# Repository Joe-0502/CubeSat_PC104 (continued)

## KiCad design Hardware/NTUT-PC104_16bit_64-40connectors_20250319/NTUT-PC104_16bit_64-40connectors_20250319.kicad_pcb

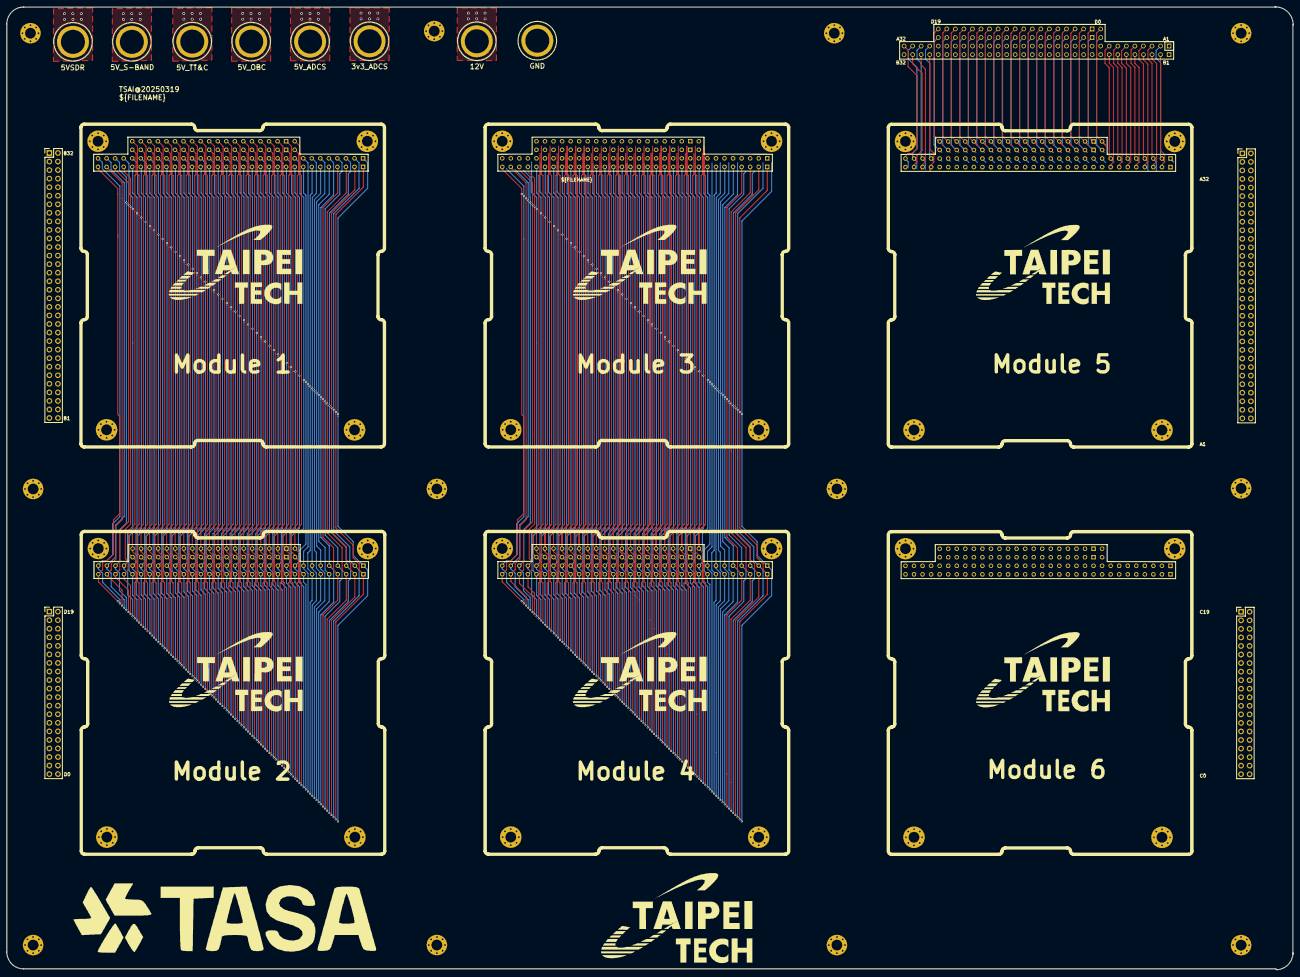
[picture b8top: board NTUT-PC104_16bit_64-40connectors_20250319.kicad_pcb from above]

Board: 4 copper layers, 382.2 x 286.1 mm, 31 parts (0 on the bottom side), 104 nets.

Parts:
H7, H7#2, H8, H9, H10, H11, H12, H13, H14, H15, H15#2, H15#3: MountingHole_Pad; MountingHole_3.2mm_M3_Pad_Via
J9, J9#2, J10, J11, J11#2, J12: CubeSat_PC104_16bit_footprint
J13: PC104_16bit_Connector
J17, J19: Conn_02x26_Odd_Even; PinHeader_2x32_P2.54mm_Vertical
J18, J20: Conn_02x26_Odd_Even; PinHeader_2x20_P2.54mm_Vertical
TP9, TP9#2, TP9#3, TP10, TP10#2, TP10#3, TP11, TP12: TestPoint_Alt; KSE_PN6095

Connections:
/A1: J9.A1, J9#2.A1, J10.A1, J11.A1, J11#2.A1, J12.A1, J13.A1, J17.63, J19.63
/A2: J9.A2, J9#2.A2, J10.A2, J11.A2, J11#2.A2, J12.A2, J13.A2, J17.61, J19.61
/A3: J9.A3, J9#2.A3, J10.A3, J11.A3, J11#2.A3, J12.A3, J13.A3, J17.59, J19.59
/A4: J9.A4, J9#2.A4, J10.A4, J11.A4, J11#2.A4, J12.A4, J13.A4, J17.57, J19.57
/A5: J9.A5, J9#2.A5, J10.A5, J11.A5, J11#2.A5, J12.A5, J13.A5, J17.55, J19.55
/A6: J9.A6, J9#2.A6, J10.A6, J11.A6, J11#2.A6, J12.A6, J13.A6, J17.53, J19.53
/A7: J9.A7, J9#2.A7, J10.A7, J11.A7, J11#2.A7, J12.A7, J13.A7, J17.51, J19.51
/A8: J9.A8, J9#2.A8, J10.A8, J11.A8, J11#2.A8, J12.A8, J13.A8, J17.49, J19.49
/A9: J9.A9, J9#2.A9, J10.A9, J11.A9, J11#2.A9, J12.A9, J13.A9, J17.47, J19.47
/A10: J9.A10, J9#2.A10, J10.A10, J11.A10, J11#2.A10, J12.A10, J13.A10, J17.45, J19.45
/A11: J9.A11, J9#2.A11, J10.A11, J11.A11, J11#2.A11, J12.A11, J13.A11, J17.43, J19.43
/A12: J9.A12, J9#2.A12, J10.A12, J11.A12, J11#2.A12, J12.A12, J13.A12, J17.41, J19.41
/A13: J9.A13, J9#2.A13, J10.A13, J11.A13, J11#2.A13, J12.A13, J13.A13, J17.39, J19.39
/A14: J9.A14, J9#2.A14, J10.A14, J11.A14, J11#2.A14, J12.A14, J13.A14, J17.37, J19.37
/A15: J9.A15, J9#2.A15, J10.A15, J11.A15, J11#2.A15, J12.A15, J13.A15, J17.35, J19.35
/A16: J9.A16, J9#2.A16, J10.A16, J11.A16, J11#2.A16, J12.A16, J13.A16, J17.33, J19.33
/A17: J9.A17, J9#2.A17, J10.A17, J11.A17, J11#2.A17, J12.A17, J13.A17, J17.31, J19.31
/A18: J9.A18, J9#2.A18, J10.A18, J11.A18, J11#2.A18, J12.A18, J13.A18, J17.29, J19.29
/A19: J9.A19, J9#2.A19, J10.A19, J11.A19, J11#2.A19, J12.A19, J13.A19, J17.27, J19.27
/A20: J9.A20, J9#2.A20, J10.A20, J11.A20, J11#2.A20, J12.A20, J13.A20, J17.25, J19.25
/A21: J9.A21, J9#2.A21, J10.A21, J11.A21, J11#2.A21, J12.A21, J13.A21, J17.23, J19.23
/A22: J9.A22, J9#2.A22, J10.A22, J11.A22, J11#2.A22, J12.A22, J13.A22, J17.21, J19.21
/A23: J9.A23, J9#2.A23, J10.A23, J11.A23, J11#2.A23, J12.A23, J13.A23, J17.19, J19.19
/A24: J9.A24, J9#2.A24, J10.A24, J11.A24, J11#2.A24, J12.A24, J13.A24, J17.17, J19.17
/A25: J9.A25, J9#2.A25, J10.A25, J11.A25, J11#2.A25, J12.A25, J13.A25, J17.15, J19.15
/A26: J9.A26, J9#2.A26, J10.A26, J11.A26, J11#2.A26, J12.A26, J13.A26, J17.13, J19.13
/A27: J9.A27, J9#2.A27, J10.A27, J11.A27, J11#2.A27, J12.A27, J13.A27, J17.11, J19.11
/A28: J9.A28, J9#2.A28, J10.A28, J11.A28, J11#2.A28, J12.A28, J13.A28, J17.9, J19.9
/A29: J9.A29, J9#2.A29, J10.A29, J11.A29, J11#2.A29, J12.A29, J13.A29, J17.7, J19.7
/A30: J9.A30, J9#2.A30, J10.A30, J11.A30, J11#2.A30, J12.A30, J13.A30, J17.5, J19.5
/A31: J9.A31, J9#2.A31, J10.A31, J11.A31, J11#2.A31, J12.A31, J13.A31, J17.3, J19.3
/A32: J9.A32, J9#2.A32, J10.A32, J11.A32, J11#2.A32, J12.A32, J13.A32, J17.1, J19.1
/B1: J9.B1, J9#2.B1, J10.B1, J11.B1, J11#2.B1, J12.B1, J13.B1, J17.64, J19.64
/B2: J9.B2, J9#2.B2, J10.B2, J11.B2, J11#2.B2, J12.B2, J13.B2, J17.62, J19.62
/B3: J9.B3, J9#2.B3, J10.B3, J11.B3, J11#2.B3, J12.B3, J13.B3, J17.60, J19.60
/B4: J9.B4, J9#2.B4, J10.B4, J11.B4, J11#2.B4, J12.B4, J13.B4, J17.58, J19.58
/B5: J9.B5, J9#2.B5, J10.B5, J11.B5, J11#2.B5, J12.B5, J13.B5, J17.56, J19.56
/B6: J9.B6, J9#2.B6, J10.B6, J11.B6, J11#2.B6, J12.B6, J13.B6, J17.54, J19.54
/B7: J9.B7, J9#2.B7, J10.B7, J11.B7, J11#2.B7, J12.B7, J13.B7, J17.52, J19.52
/B8: J9.B8, J9#2.B8, J10.B8, J11.B8, J11#2.B8, J12.B8, J13.B8, J17.50, J19.50
/B9: J9.B9, J9#2.B9, J10.B9, J11.B9, J11#2.B9, J12.B9, J13.B9, J17.48, J19.48
/B10: J9.B10, J9#2.B10, J10.B10, J11.B10, J11#2.B10, J12.B10, J13.B10, J17.46, J19.46
/B11: J9.B11, J9#2.B11, J10.B11, J11.B11, J11#2.B11, J12.B11, J13.B11, J17.44, J19.44
/B12: J9.B12, J9#2.B12, J10.B12, J11.B12, J11#2.B12, J12.B12, J13.B12, J17.42, J19.42
/B13: J9.B13, J9#2.B13, J10.B13, J11.B13, J11#2.B13, J12.B13, J13.B13, J17.40, J19.40
/B14: J9.B14, J9#2.B14, J10.B14, J11.B14, J11#2.B14, J12.B14, J13.B14, J17.38, J19.38
/B15: J9.B15, J9#2.B15, J10.B15, J11.B15, J11#2.B15, J12.B15, J13.B15, J17.36, J19.36
/B16: J9.B16, J9#2.B16, J10.B16, J11.B16, J11#2.B16, J12.B16, J13.B16, J17.34, J19.34
/B17: J9.B17, J9#2.B17, J10.B17, J11.B17, J11#2.B17, J12.B17, J13.B17, J17.32, J19.32
/B18: J9.B18, J9#2.B18, J10.B18, J11.B18, J11#2.B18, J12.B18, J13.B18, J17.30, J19.30
/B19: J9.B19, J9#2.B19, J10.B19, J11.B19, J11#2.B19, J12.B19, J13.B19, J17.28, J19.28
/B20: J9.B20, J9#2.B20, J10.B20, J11.B20, J11#2.B20, J12.B20, J13.B20, J17.26, J19.26
/B21: J9.B21, J9#2.B21, J10.B21, J11.B21, J11#2.B21, J12.B21, J13.B21, J17.24, J19.24
/B22: J9.B22, J9#2.B22, J10.B22, J11.B22, J11#2.B22, J12.B22, J13.B22, J17.22, J19.22
/B23: J9.B23, J9#2.B23, J10.B23, J11.B23, J11#2.B23, J12.B23, J13.B23, J17.20, J19.20
/B24: J9.B24, J9#2.B24, J10.B24, J11.B24, J11#2.B24, J12.B24, J13.B24, J17.18, J19.18
/B25: J9.B25, J9#2.B25, J10.B25, J11.B25, J11#2.B25, J12.B25, J13.B25, J17.16, J19.16
/B26: J9.B26, J9#2.B26, J10.B26, J11.B26, J11#2.B26, J12.B26, J13.B26, J17.14, J19.14
/B27: J9.B27, J9#2.B27, J10.B27, J11.B27, J11#2.B27, J12.B27, J13.B27, J17.12, J19.12
/B28: J9.B28, J9#2.B28, J10.B28, J11.B28, J11#2.B28, J12.B28, J13.B28, J17.10, J19.10
/B29: J9.B29, J9#2.B29, J10.B29, J11.B29, J11#2.B29, J12.B29, J13.B29, J17.8, J19.8
/B30: J9.B30, J9#2.B30, J10.B30, J11.B30, J11#2.B30, J12.B30, J13.B30, J17.6, J19.6
/B31: J9.B31, J9#2.B31, J10.B31, J11.B31, J11#2.B31, J12.B31, J13.B31, J17.4, J19.4
/B32: J9.B32, J9#2.B32, J10.B32, J11.B32, J11#2.B32, J12.B32, J13.B32, J17.2, J19.2
/C0: J9.C0, J9#2.C0, J10.C0, J11.C0, J11#2.C0, J12.C0, J13.C0, J18.39, J20.39
/C1: J9.C1, J9#2.C1, J10.C1, J11.C1, J11#2.C1, J12.C1, J13.C1, J18.37, J20.37
/C2: J9.C2, J9#2.C2, J10.C2, J11.C2, J11#2.C2, J12.C2, J13.C2, J18.35, J20.35
/C3: J9.C3, J9#2.C3, J10.C3, J11.C3, J11#2.C3, J12.C3, J13.C3, J18.33, J20.33
/C4: J9.C4, J9#2.C4, J10.C4, J11.C4, J11#2.C4, J12.C4, J13.C4, J18.31, J20.31
/C5: J9.C5, J9#2.C5, J10.C5, J11.C5, J11#2.C5, J12.C5, J13.C5, J18.29, J20.29
/C6: J9.C6, J9#2.C6, J10.C6, J11.C6, J11#2.C6, J12.C6, J13.C6, J18.27, J20.27
/C7: J9.C7, J9#2.C7, J10.C7, J11.C7, J11#2.C7, J12.C7, J13.C7, J18.25, J20.25
/C8: J9.C8, J9#2.C8, J10.C8, J11.C8, J11#2.C8, J12.C8, J13.C8, J18.23, J20.23
/C9: J9.C9, J9#2.C9, J10.C9, J11.C9, J11#2.C9, J12.C9, J13.C9, J18.21, J20.21
/C10: J9.C10, J9#2.C10, J10.C10, J11.C10, J11#2.C10, J12.C10, J13.C10, J18.19, J20.19
/C11: J9.C11, J9#2.C11, J10.C11, J11.C11, J11#2.C11, J12.C11, J13.C11, J18.17, J20.17
/C12: J9.C12, J9#2.C12, J10.C12, J11.C12, J11#2.C12, J12.C12, J13.C12, J18.15, J20.15
/C13: J9.C13, J9#2.C13, J10.C13, J11.C13, J11#2.C13, J12.C13, J13.C13, J18.13, J20.13
/C14: J9.C14, J9#2.C14, J10.C14, J11.C14, J11#2.C14, J12.C14, J13.C14, J18.11, J20.11
/C15: J9.C15, J9#2.C15, J10.C15, J11.C15, J11#2.C15, J12.C15, J13.C15, J18.9, J20.9
/C16: J9.C16, J9#2.C16, J10.C16, J11.C16, J11#2.C16, J12.C16, J13.C16, J18.7, J20.7
/C17: J9.C17, J9#2.C17, J10.C17, J11.C17, J11#2.C17, J12.C17, J13.C17, J18.5, J20.5
/C18: J9.C18, J9#2.C18, J10.C18, J11.C18, J11#2.C18, J12.C18, J13.C18, J18.3, J20.3
/C19: J9.C19, J9#2.C19, J10.C19, J11.C19, J11#2.C19, J12.C19, J13.C19, J18.1, J20.1
/D0: J9.D0, J9#2.D0, J10.D0, J11.D0, J11#2.D0, J12.D0, J13.D0, J18.40, J20.40
/D1: J9.D1, J9#2.D1, J10.D1, J11.D1, J11#2.D1, J12.D1, J13.D1, J18.38, J20.38
/D2: J9.D2, J9#2.D2, J10.D2, J11.D2, J11#2.D2, J12.D2, J13.D2, J18.36, J20.36
/D3: J9.D3, J9#2.D3, J10.D3, J11.D3, J11#2.D3, J12.D3, J13.D3, J18.34, J20.34
/D4: J9.D4, J9#2.D4, J10.D4, J11.D4, J11#2.D4, J12.D4, J13.D4, J18.32, J20.32
/D5: J9.D5, J9#2.D5, J10.D5, J11.D5, J11#2.D5, J12.D5, J13.D5, J18.30, J20.30
/D6: J9.D6, J9#2.D6, J10.D6, J11.D6, J11#2.D6, J12.D6, J13.D6, J18.28, J20.28
/D7: J9.D7, J9#2.D7, J10.D7, J11.D7, J11#2.D7, J12.D7, J13.D7, J18.26, J20.26
/D8: J9.D8, J9#2.D8, J10.D8, J11.D8, J11#2.D8, J12.D8, J13.D8, J18.24, J20.24
/D9: J9.D9, J9#2.D9, J10.D9, J11.D9, J11#2.D9, J12.D9, J13.D9, J18.22, J20.22
/D10: J9.D10, J9#2.D10, J10.D10, J11.D10, J11#2.D10, J12.D10, J13.D10, J18.20, J20.20
/D11: J9.D11, J9#2.D11, J10.D11, J11.D11, J11#2.D11, J12.D11, J13.D11, J18.18, J20.18
/D12: J9.D12, J9#2.D12, J10.D12, J11.D12, J11#2.D12, J12.D12, J13.D12, J18.16, J20.16
/D13: J9.D13, J9#2.D13, J10.D13, J11.D13, J11#2.D13, J12.D13, J13.D13, J18.14, J20.14
/D14: J9.D14, J9#2.D14, J10.D14, J11.D14, J11#2.D14, J12.D14, J13.D14, J18.12, J20.12
/D15: J9.D15, J9#2.D15, J10.D15, J11.D15, J11#2.D15, J12.D15, J13.D15, J18.10, J20.10
/D16: J9.D16, J9#2.D16, J10.D16, J11.D16, J11#2.D16, J12.D16, J13.D16, J18.8, J20.8
/D17: J9.D17, J9#2.D17, J10.D17, J11.D17, J11#2.D17, J12.D17, J13.D17, J18.6, J20.6
/D18: J9.D18, J9#2.D18, J10.D18, J11.D18, J11#2.D18, J12.D18, J13.D18, J18.4, J20.4
/D19: J9.D19, J9#2.D19, J10.D19, J11.D19, J11#2.D19, J12.D19, J13.D19, J18.2, J20.2

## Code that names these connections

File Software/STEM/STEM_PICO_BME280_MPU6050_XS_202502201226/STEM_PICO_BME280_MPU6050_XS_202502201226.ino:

// code for Pro Micro or STM32 on the CubeSat Simulator STEM Payload board
// answers "OK" on the serial port Serial1 when queried by the Pi

#include <Wire.h>
#include <Adafruit_Sensor.h>
#include <Adafruit_BME280.h>
#include <MPU6050_tockn.h>
#include <EEPROM.h>
#define SEALEVELPRESSURE_HPA (1013.25)


// Code modified for STEM board with PICO 

// PI_TXD       : GPIO0   using Serial1()
// PI_RXD       : GPIO1
// TX2          : GPIO8   using Serial2()
// RX2          : GPIO9
// LED1(G)      : GPIO17
// LED2(B)      : GPIO16
// LED(BUILT_IN): GPIO14

// I2C0_SDA     : GPIO12
// I2C0_SCL     : GPIO13
// I2C1_SDA     : GPIO6
// I2C1_SCL     : GPIO7

Adafruit_BME280 bme;
MPU6050 mpu6050(Wire);


long timer = 0;
int bmePresent;
int RXLED = LED_BUILTIN;  // The RX LED has a defined Arduino pin
int greenLED = 19;
int blueLED = 18;
int Sensor1 = 0;
float Sensor2 = 0;
void eeprom_word_write(int addr, int val);
short eeprom_word_read(int addr);
int first_time = true;
int first_read = true;

float T2 = 25; // Temperature data point 1
float R2 = 671; // Reading data point 1
float T1 = 15.5; // Temperature data point 2
float R1 = 695; // Reading data point 2


int sensorValue;
float Temp;
float rest;
  
void setup() {

  Serial2.begin(115200); // Serial Monitor for testing
  Serial1.begin(115200);  // UART1 faster speed
  Serial2.println("UART1: Starting!");

  Wire.setSCL(13);
  Wire.setSDA(12);
  Wire.begin();
  
  blink_setup();
 
  blink(500);
  delay(250);
  blink(500);
  delay(250);
  led_set(greenLED, HIGH);
  delay(250);
  led_set(greenLED, LOW);
  led_set(blueLED, HIGH);
  delay(250);
  led_set(blueLED, LOW);

  if (bme.begin(0x76)) {
    bmePresent = 1;
  } else {
    Serial2.println("UART1: Could not find a valid BME280 sensor, check wiring!");
    bmePresent = 0;
  }
 
  mpu6050.begin();
 
  if (eeprom_word_read(0) == 0xA07)
  {
    Serial2.println("UART1: Reading gyro offsets from EEPROM\n");
 
    float xOffset = ((float)eeprom_word_read(1)) / 100.0;
    float yOffset = ((float)eeprom_word_read(2)) / 100.0;
    float zOffset = ((float)eeprom_word_read(3)) / 100.0;
 
    Serial2.println(xOffset, DEC);
    Serial2.println(yOffset, DEC);
    Serial2.println(zOffset, DEC);
 
    mpu6050.setGyroOffsets(xOffset, yOffset, zOffset);
  }
  else
  {
    Serial2.println("UART1: Calculating gyro offsets and storing in EEPROM\n");
 
    mpu6050.calcGyroOffsets(true);
 
    eeprom_word_write(0, 0xA07);
    eeprom_word_write(1, (int)(mpu6050.getGyroXoffset() * 100.0) + 0.5);
    eeprom_word_write(2, (int)(mpu6050.getGyroYoffset() * 100.0) + 0.5);
    eeprom_word_write(3, (int)(mpu6050.getGyroZoffset() * 100.0) + 0.5);
 
    Serial2.println(eeprom_word_read(0), HEX);
    Serial2.println(((float)eeprom_word_read(1)) / 100.0, DEC);
    Serial2.println(((float)eeprom_word_read(2)) / 100.0, DEC);
    Serial2.println(((float)eeprom_word_read(3)) / 100.0, DEC);
  }
/**/      
  Serial2.println("UART1: Done with Setup()");
}
 
void loop() {
 
  if (Serial1.available() > 0) {
    blink(50);
    char result = Serial1.read();
//  Serial1.println(result);
//  Serial1.println("OK");
 
//    if (result == '?')
    {
      if (bmePresent) {
        Serial1.print("OK BME280 ");
        Serial1.print(bme.readTemperature());
        Serial1.print(" ");
        Serial1.print(bme.readPressure() / 100.0F);
        Serial1.print(" ");
        Serial1.print(bme.readAltitude(SEALEVELPRESSURE_HPA));
        Serial1.print(" ");
        Serial1.print(bme.readHumidity());
      } else
      {
        Serial1.print("OK BME280 0.0 0.0 0.0 0.0");
      }
      mpu6050.update();
 
      Serial1.print(" MPU6050 ");
      Serial1.print(mpu6050.getGyroX());
      Serial1.print(" ");
      Serial1.print(mpu6050.getGyroY());
      Serial1.print(" ");
      Serial1.print(mpu6050.getGyroZ());
 
    Serial1.print(" ");
    Serial1.print(mpu6050.getAccX());   
    Serial1.print(" ");
    Serial1.print(mpu6050.getAccY());   
    Serial1.print(" ");
    Serial1.print(mpu6050.getAccZ());   
 
    sensorValue = read_analog();
    Sensor2 = analogRead(1)*3.3/1024;
//  Serial.println(sensorValue);  
    Temp = T1 + (sensorValue - R1) *((T2 - T1)/(R2 - R1));
 
    Serial1.print(" XS ");
    Serial1.print(Temp);   
    Serial1.print(" ");
    Serial1.println(Sensor2);              
     
    float rotation = sqrt(mpu6050.getGyroX()*mpu6050.getGyroX() + mpu6050.getGyroY()*mpu6050.getGyroY() + mpu6050.getGyroZ()*mpu6050.getGyroZ()); 
    float acceleration = sqrt(mpu6050.getAccX()*mpu6050.getAccX() + mpu6050.getAccY()*mpu6050.getAccY() + mpu6050.getAccZ()*mpu6050.getAccZ()); 
//    Serial.print(rotation);
//    Serial.print(" ");
//    Serial.println(acceleration);
 
    if (first_read == true) {
      first_read = false;
      rest = acceleration;
    }
 
    if (acceleration > 1.2 * rest)
        led_set(greenLED, HIGH);
    else
        led_set(greenLED, LOW);
        
    if (rotation > 5)
        led_set(blueLED, HIGH);
    else
        led_set(blueLED, LOW);
    }
   
  }

  if (Serial2.available() > 0) {
    blink(50);
    char result = Serial2.read();
//    Serial.println(result);
//    Serial.println("OK");
//    Serial.println(counter++); 
   
  if (result == 'R') {
      Serial2.println("UART1: OK");
      delay(100);
      first_read = true;
      setup();
    }
  else if (result == 'C') {
      Serial2.println("UART1: Clearing stored gyro offsets in EEPROM\n");
      eeprom_word_write(0, 0x00);
      first_time = true;
      setup();
    }  
   
 if ((result == '?') || first_time == true)
    {
      first_time = false;
      if (bmePresent) {
        Serial2.print("UART1: OK BME280 ");
        Serial2.print(bme.readTemperature());
        Serial2.print(" ");
        Serial2.print(bme.readPressure() / 100.0F);
        Serial2.print(" ");
        Serial2.print(bme.readAltitude(SEALEVELPRESSURE_HPA));
        Serial2.print(" ");
        Serial2.print(bme.readHumidity());
      } else
      {
        Serial2.print("UART1: OK BME280 0.0 0.0 0.0 0.0");
      }
      mpu6050.update();
 
      Serial2.print(" MPU6050 ");
      Serial2.print(mpu6050.getGyroX());
      Serial2.print(" ");
      Serial2.print(mpu6050.getGyroY());
      Serial2.print(" ");
      Serial2.print(mpu6050.getGyroZ());
 
    Serial2.print(" ");
    Serial2.print(mpu6050.getAccX());   
    Serial2.print(" ");
    Serial2.print(mpu6050.getAccY());   
    Serial2.print(" ");
    Serial2.print(mpu6050.getAccZ());   
    
    sensorValue = read_analog();
    Sensor2 = analogRead(A1)*3.3/512;

    Temp = T1 + (sensorValue - R1) *((T2 - T1)/(R2 - R1));
 
    Serial2.print(" XS ");
    Serial2.print(Temp);   
    Serial2.print(" ");
    Serial2.print(Sensor2);              
    Serial2.print(" (");  
    Serial2.print(sensorValue);   
    Serial2.println(")"); 
  
    float rotation = sqrt(mpu6050.getGyroX()*mpu6050.getGyroX() + mpu6050.getGyroY()*mpu6050.getGyroY() + mpu6050.getGyroZ()*mpu6050.getGyroZ()); 
    float acceleration = sqrt(mpu6050.getAccX()*mpu6050.getAccX() + mpu6050.getAccY()*mpu6050.getAccY() + mpu6050.getAccZ()*mpu6050.getAccZ()); 
//    Serial.print(rotation);
//    Serial.print(" ");
//    Serial.println(acceleration);
 
    if (first_read == true) {
      first_read = false;
      rest = acceleration;
    }
 
    if (acceleration > 1.2 * rest)
        led_set(greenLED, HIGH);
    else
        led_set(greenLED, LOW);
        
    if (rotation > 5)
        led_set(blueLED, HIGH);
    else
        led_set(blueLED, LOW);
    }
  }  
  delay(100);
}
 
void eeprom_word_write(int addr, int val)
{
  EEPROM.write(addr * 2, lowByte(val));
  EEPROM.write(addr * 2 + 1, highByte(val));
}
 
short eeprom_word_read(int addr)
{
  return ((EEPROM.read(addr * 2 + 1) << 8) | EEPROM.read(addr * 2));
}
 
void blink_setup() 
{
  // initialize digital pin PB1 as an output.
  pinMode(RXLED, OUTPUT);
  pinMode(greenLED, OUTPUT);
  pinMode(blueLED, OUTPUT);
 
}
 
void blink(int length)
{
  digitalWrite(RXLED, HIGH);   // turn the LED on (HIGH is the voltage level)
 
  delay(length);              // wait for a lenth of time
 
  digitalWrite(RXLED, LOW);    // turn the LED off by making the voltage LOW

}
 
void led_set(int ledPin, bool state)
{
  if (ledPin == greenLED)
    digitalWrite(greenLED, state);
  else if (ledPin == blueLED)
    digitalWrite(blueLED, state);    

}

int read_analog()
{
    int sensorValue;
    sensorValue = analogRead(A2);

    return(sensorValue); 
}

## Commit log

2025-03-13 Add files via upload
    CubeSatSim_PC104 Board
2025-03-13 Add files via upload
    INA219 Purple Board
2025-03-13 Add files via upload
    TPS61230 5V booster
2025-03-13 Rename AMSAT_Battery_PC104_20250312.kicad_dru to AMSAT_Battery_PC104_20250312.kicad_dru
2025-03-13 Add files via upload
    CubesatSim_Battery_PC104
2025-03-13 Add files via upload
    CubesatSim_Main_PC104 Right
2025-03-13 Add files via upload
    CubeSatSim_STEM_PC104 Right
2025-03-13 Create Readme
    Folders for KiCAD Symbols and Footprints
2025-03-13 Create Readme
    Symbol Files
2025-03-13 Add files via upload
    LOGO footprints
2025-03-20 20250320
2025-03-20 Create TPS61230_Booster_5V_Layout-240812_JLCPCB
2025-03-20 TPS61230
2025-03-20 Move TPS61230_Booster_5V_Layout-240812_JLCPCB to hardware directory.
2025-03-21 Upgrade TPS61230_Booster_5V_Layout-240812_JLCPCB to Kicad 8.
2025-03-21 Modify Schematic, assign GND to mount holes. Modify 64-pin and 40-pin labels.
2025-03-22 1. Add all six boards. 2. Assign Parus pins to every board. 3. Change foot-print path to project directory such that the project will not rely on external footprints. 4. Copy 'CubeSat_PC104_16bit_foo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
2025-03-22 Move all hardware related to 'Hardware' directory.
2025-03-22 1. Add CubesatSim Main and Battery files. 2. Add .gitignore such that proeuction/ directories are not pushed to github repo.
2025-03-22 Add INA219_0603_SOT23-8_JLCPCB Kicad design files.
2025-03-22 Add addition patterns in .gitignore.
2025-03-31 20250331_v1
2025-03-31 20250331_v2
2025-04-01 Securely connect Module 3 to its PC104 connector. Then, set the PCB design rules to match JLCPCB's specifications.
2025-04-01 Copper Pour
2025-04-02 Modify the pins below the banana socket
2025-04-02 1. Add power zones to associated pins on Left-up module. 2. Correct net names, i.e., upper/lower cases of net names.
2025-04-03 5v SDR copper
2025-04-03 5v SDR copper,PC/104 Module 3 Connections
2025-04-03 1. All power zones added.
2025-04-03 1. Create new project, 'NTUT-PC104_16bit_64-40connectors_20250326-2025-04-03_v3.kicad_pro'. 2. Add custom design rule based on capabilities of JLCPCB.
2025-04-03 1. Connections between J5-J11 done. 2. Correct upper/lower case of J11.
2025-04-05 1. Traces and Pads of 5V_SDR_10W were messed up. Need to be adjusted properly. 2. When copying tracks from one pad to another pad, using F.Cu layer first, changing layer afterward. 3. This PCB needs 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
2025-04-05 1. 9.0.0 works ok. Cause of net mess up was the zones. Remove zones solve the problem. 2. upper portion is almost done.
2025-04-06 1. Layout completed. 2. Isolated copper zone ignored. 3. Needs to validate and verify the layout completely.
2025-04-06 1. Copy 'PC104_16bit_Connector.kicad_mod', 'NTUT_logo_40mm.kicad_mod', and 'TASA_LOGO_90mm.kicad_mod' to VST104-Libraries. 2. DRC check without any error and warning.
2025-04-07 1. Confirmed from TASA, B11 and A21 are electrically connected. The labels of B11 on all connectors are changed to 'OUTPW1'. 2. Traces of B11 and A21 are now connected.
2025-04-08 1. Change Label of B11 back to OUTPW1_1 according to suggestion from TASA. 2. Need to verify and validate the traces again.
2025-04-15 Module 2 Module 4 dc_bus_1 repaint
2025-05-01 Update power connections of Battery Board for PARUS pin assignments.
2025-05-01 STEM_Board,Main_Board PC104 pinout update
2025-05-06 1. Swap I2C connector and temperature sensor on STEM board. 2. Add marks on side connectors. 3. Copy FlatSat project to new project dated 20250506. Update date on flatsat board.
2025-05-06 1. In NTUT-PC104_16bit_64-40connectors_2025-05-07_v4.1, add third row for every power pin header so the jumpercap can be placed when them are not used.
2025-05-06 Add a new PCB view image file.
2025-05-13 STEM_pico_20250513
2025-05-16 Add TPS61033x Booster boards for evaluation and CubeSatSim.
2025-05-24 1. In NTUT-PC104_16bit_64-40connectors_2025-05-24_v4.2, reroute 5V_OBC_5W.
